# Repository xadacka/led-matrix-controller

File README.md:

Note: This is still beta and will be changing and needs to be tidied up a bit but it all works pretty well, just install it and control it from the web interface. There is a huge update coming soon that redesigns the entire interface and back end, stay tuned for that it'll make the whole thing 10x more usable and stable, along with making it easy too update the animations.

led-matrix-controller
=====================
Web based controller for led panels. This code is designed for Raspberry Pi using HUB75 led panels. You can buy the panels cheap from China, or get them off eBay or adafruit or a multitude of other places.

To use this code, simply run the command below.

```
curl -sSL https://raw.githubusercontent.com/xadacka/led-matrix-controller/master/setup.sh | bash
```

The setup script will install apache2 and move the required files into the web directory and change a few permissions for apache. The only way this can work is by letting www-data (apache, php) access the GPIO pins. By default, they require sudo - the setup script allows www-data to access them. This is a minor security issue but shouldn't be too bad.

Notes on screen size/chain length
----------------------------------
Currently, the code is designed for 4 32x16 panels in series from chain 1 - will soon be adding an option on the web interface for changing how many panels you have and how they're chained. You can manually change this now to add/remove panels by changing the flags in the bash scripts, namely the important ones are as follows.

For text: [piyhon.py](rpi-rgb-led-matrix/examples-api-use/pithon.py)
For clock: [time.sh](rpi-rgb-led-matrix/examples-api-use/time.sh)
For animations: Every script in [scripts](scripts)

Simple change --led-rows=16 to how many pixels high your panels are and --led-chain=4 to the amount of panels you're using.

Automated Setup
---------------
We strongly recommend running raspbian-lite as opposed to the full version, you can download the image [here](https://www.raspberrypi.org/downloads/raspbian/)

You should probably wire the panels before running the scripts as once it's installed, it'll show you the pi's IP on the screen but you can leave that until after if you like. Wiring diagram is [here](./wiring.md)

To use this code, simply run the command below. 

The setup script will clone into /home/pi - as of now it'll only work in this folder.

Of course, piping unknown scripts into bash isn't generally good security policy but if you've any doubts just take a look at the install script yourself and you'll see all is in order.

```
curl -sSL https://raw.githubusercontent.com/xer0design/led-matrix-controller/master/setup.sh | bash
```

This will automate everything and will reboot after, once the reboot is finished you should see your Pi's IP address scrolling across the screen and from there, you can type it into your browser and start using your panel.

The default password for the web interface is "password". Because of course it is. 

Manual Setup
------------
We wouldn't recommend it. But we will add instructions soon. If you want, just open [setup.sh](./setup.sh) to see what's happening, it's all commented out.

Basic configuration
===================

Password Management
-------------------
As default, the password protected access is both not fully enabled, and set to the default password "password". You should fix both of these things in a live environment. If go just type [/sender.php](/www/sender.php) after the pi's ip address, you'll have full control without the need to login. This is useful on closed networks and when testing (so you don't get logged out every few minutes), but to enable password verification for the sender screen, you'll need to edit [sender.php](/www/sender.php) and remove the comments from the first section. This will ensure no one else can access your system. This is especially important considering some scripts can be run with sudo through the web ui - not ideal. 

To change the password, modify [login.php](www/login.php) and edit the third line - obviously, you should also enable password authentication on sender.php as listed above.

Fonts
-----
If you're not too fond of the standard font, American Captain, that's cool, we get it, it's quite easy to change. Edit the file [pithon.py](rpi-rgb-led-matrix/examples-api-use/pithon.py) (yes, we're awful at naming files). You'll see a few examples listed but commented out, just comment out the standard font and uncomment an alternative. If none of them do it for you, you can copy any .ttf font you like into the directory and link to it. In fact, it doesn't even have to be in the same directory. You may have to change the font size when selecting something else. 

Animations
----------
There are many included animations, to use these just select the one you want on the web interface and click submit. I personally use this code myself for work in bars and clubs so the included animations are mostly drinks company logos and the like. I've included a photoshop file animations.psd which should make it easy to drop your own images in and replicate the animations. Or, of course, you can make your own from scratch. To add them to the web interface, edit senders.php to include links to your files, or if you want just point the premade ones to your own files if you don't plan on using mine.

Animations should be made the same size as your display. I.E. if you're using 2 32x16 panels, make sure your animations are 64x16 and so on.) As of 1.5, we cloned the most recent code from [Hzeller](https://github.com/hzeller/rpi-rgb-led-matrix), so we now have video functionality, but we haven't added any standard examples yet. h.264 seems to run very well, so we'd recommend that. 

External Refrences
------------------
You'll see a few refrences to an external folder and also to a few external files, you can ignore these and delete the refrences, or you can make use of them and add in your own external files, or you can just leave them there - it won't effect performance in any meaningful way. I use this code primarily for myself along side another system which the external code controls.

Copyright & Licensing
=====================
We've no doubts you know how GPL 3.0 works, but just to make things extra clear, you're fully allowed to use this code for both personal and commercial use, but you must keep all copyright notices in tact and share your changes under the same conditions. 
You can change the title section of the page if you like, the xer0.design led-matrix-controller vX.X bit with the icon, but the footer must be kept under all circumstances, along with notices inside the code. This code is offered as-is, with no warranty.

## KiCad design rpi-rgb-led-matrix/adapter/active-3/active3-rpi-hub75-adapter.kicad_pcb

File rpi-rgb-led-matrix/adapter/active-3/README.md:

Adapter PCB to support up to 3 panel chains
===========================================

   * Supports up to three panel chains for newer plus models and
     Raspberry Pi 2 that have 40 GPIO pins.
   * Uses HCT245 to level shift signals from 3.3V to 5V and shield
     the Raspberry Pi GPIOs from overloading.
   * Open source KiCAD PCB EDA format.
   * Optional: Pads to power the Pi with 5V, including optional capacitor footprints.
   * Connector for RxD input (literally the only GPIO pin left) in case you want to
     make your panel controlled with a serial interface (3.3V logic level).
   * Provides a way to choose the pinout for different kinds of 64x64 matrixes.
   * (not very pretty layout, was just lazy and let the auto-router generate the first pass)
   * BOM:
     - 4x 74HCT245 or 74AHCT245 in 20-SOIC, 7.5mm package which should make
     it easy to hand-solder. Make sure to get the variant with the **T**: HC**T** or AHC**T**
     (there are also HC or AHC, don't use these).
     - 4x 100nF ceramic capacitor (0805 package)
     - 1x 10kOhm resistor (0805 package). Not critcial, just a pullup (2.2k .. 15k probably ok).
     - 3x 16pin IDC (=2x8) male receptible to connect the panels.
     - 1x 40pin female connector to connect to the RPi.
     - 1x (optional) 22μF .. 100μF capacitor for 5V rail.
   * The Gerber FAB files are provided as [active3-rpi-hub75-adapter-fab.zip](./active3-rpi-hub75-adapter-fab.zip)

The board is also [shared on OSH Park][osh-active3] (not affiliated).

![Preview][rendering]
![Real World][real-world]

Essentially, this is connecting the output pins through level shifting buffers (they
are operated at 5V, but the HCT series chips accept 3.3V input levels from the Pi). The
strobe, OE and clock signals are separately buffered for each connector.

![Schematic][schematic]

## Optional

### Power in

The area on the left has 5V/GND input pads, that allow you to power your Raspberry Pi from
a 5V source ... which you are likely to have as you are powering the LED Matrix. This is often
more convenient than using the USB connector to power the Pi.

If you do that, there are pads to add a capacitor to smooth the supply - two footprints are
provided: C5 and C6 for through-hole or surface mount components. The value is not critical;
I usually use a 22μF/6.3V ceramic capacitor on the C6 pads.

### Choose E-Line for 64x64 panels with 1:32 multiplexing

If you have a 64x64 matrix with 1:32 multiplexing, you need to supply an `E`-address line to it.
While the Address lines `A` to `D` have fixed positions on the Hub75 connector, there
seem to be two different ways to connect the `E` address line: it is either on pin 4 or pin 8
of the connector. So this adapter board provides the flexibility to choose the right pin for
your matrix.

Look at the back of the matrix or the documentation to find out for your specific board where
to connect E.

Once you know that, the jumper area in the bottom left of this adapter board allows to choose
to which pin to connect the E-address line to. The corresponding other pin should be connected
to GND. Simply solder a wire bridge as indicated below (or use a jumper that you can change later).

If you are not using such 64x64 matrix, you can connect both these pins to GND.

Here are the typical configurations:

No 1:32 64x64: to GND    | E-Line on Pin 4   | E-Line on Pin 8|
-------------------------|-------------------|----------------
![][config-default]      |![][config-pin4]   |![][config-pin8]

### Input for serial RxD

If you are not using a 64x64 display that occupies the E-Line, you can use the RxD serial input -
this might come in handy if you are using the display to be controlled by a serial line. Be aware
that the input requires 3.3V level, so if you have a RS232, make sure to first adapt the levels.

[rendering]: ../../img/active3-pcb.png
[config-default]: ../../img/active3-pcb-config-default.png
[config-pin4]: ../../img/active3-pcb-config-pin4.png
[config-pin8]: ../../img/active3-pcb-config-pin8.png
[schematic]: ../../img/active3-schematic.png
[real-world]: ../../img/three-parallel-panels-soic.jpg
[osh-active3]: https://oshpark.com/shared_projects/bFtff2GR

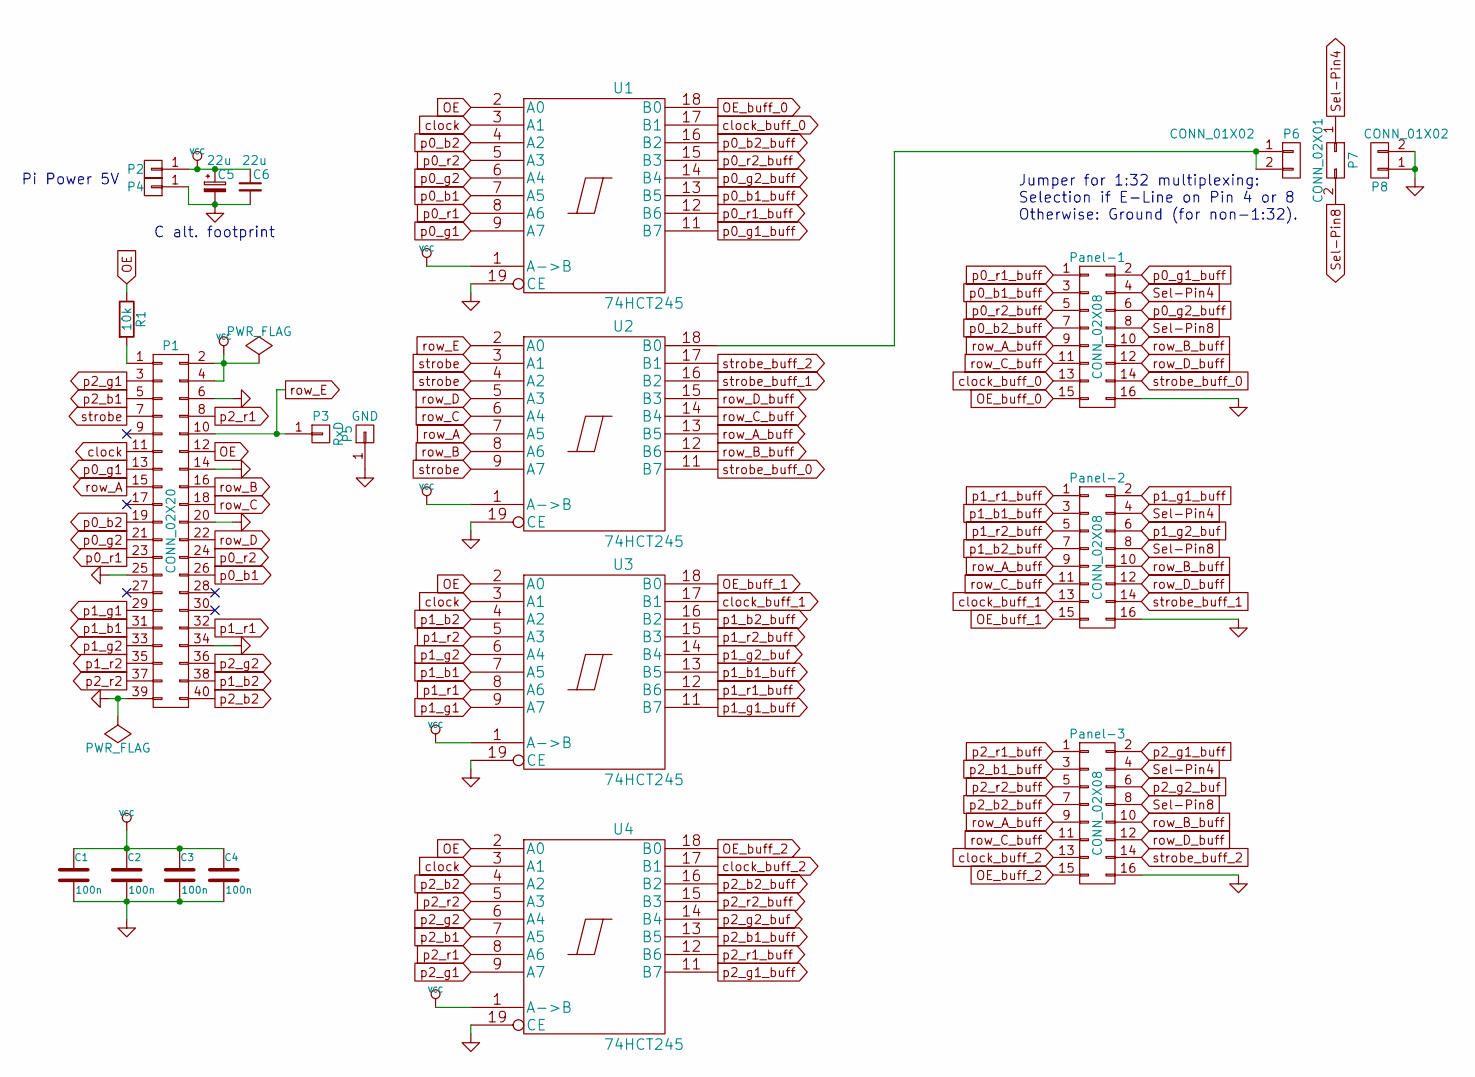
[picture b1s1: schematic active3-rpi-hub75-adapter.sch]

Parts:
C1, C2, C3, C4: 100n; C_0805_HandSoldering
C5: 22u; C_Radial_D6.3_L11.2_P2.5
C6: 22u; C_1206_HandSoldering
P1: CONN_02X20; Pin_Header_Straight_2x20
P2: +5V; Pin_Header_Straight_1x01
P3: RxD; Pin_Header_Straight_1x01
P4, P5: GND; Pin_Header_Straight_1x01
P6, P8: CONN_01X02; Pin_Header_Straight_1x02
P7: CONN_02X01; Pin_Header_Straight_1x02
Panel-1, Panel-2, Panel-3: CONN_02X08; Pin_Header_Straight_2x08
R1: 10k; R_0805_HandSoldering
U1, U2, U3, U4: 74HCT245; SOIC-20_7.5x12.8mm_Pitch1.27mm

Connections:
GND: C1.2, C2.2, C3.2, C4.2, C5.2, C6.2, P1.6, P1.14, P1.20, P1.25, P1.34, P1.39, P4.1, P5.1, P8.1, P8.2, Panel-1.16, Panel-2.16, Panel-3.16, U1.10 (GND), U1.19 (CE), U2.10 (GND), U2.19 (CE), U3.10 (GND), U3.19 (CE), U4.10 (GND), U4.19 (CE)
unnamed: P1.1, R1.2
unnamed: P6.1, P6.2, U2.18 (B0)
OE: P1.12, R1.1, U1.2 (A0), U3.2 (A0), U4.2 (A0)
OE_buff_0: Panel-1.15, U1.18 (B0)
OE_buff_1: Panel-2.15, U3.18 (B0)
OE_buff_2: Panel-3.15, U4.18 (B0)
Sel-Pin4: P7.1, Panel-1.4, Panel-2.4, Panel-3.4
Sel-Pin8: P7.2, Panel-1.8, Panel-2.8, Panel-3.8
VCC: C1.1, C2.1, C3.1, C4.1, C5.1, C6.1, P1.2, P1.4, P2.1, U1.1 (A->B), U1.20 (VCC), U2.1 (A->B), U2.20 (VCC), U3.1 (A->B), U3.20 (VCC), U4.1 (A->B), U4.20 (VCC)
clock: P1.11, U1.3 (A1), U3.3 (A1), U4.3 (A1)
clock_buff_0: Panel-1.13, U1.17 (B1)
clock_buff_1: Panel-2.13, U3.17 (B1)
clock_buff_2: Panel-3.13, U4.17 (B1)
p0_b1: P1.26, U1.7 (A5)
p0_b1_buff: Panel-1.3, U1.13 (B5)
p0_b2: P1.19, U1.4 (A2)
p0_b2_buff: Panel-1.7, U1.16 (B2)
p0_g1: P1.13, U1.9 (A7)
p0_g1_buff: Panel-1.2, U1.11 (B7)
p0_g2: P1.21, U1.6 (A4)
p0_g2_buff: Panel-1.6, U1.14 (B4)
p0_r1: P1.23, U1.8 (A6)
p0_r1_buff: Panel-1.1, U1.12 (B6)
p0_r2: P1.24, U1.5 (A3)
p0_r2_buff: Panel-1.5, U1.15 (B3)
p1_b1: P1.31, U3.7 (A5)
p1_b1_buff: Panel-2.3, U3.13 (B5)
p1_b2: P1.38, U3.4 (A2)
p1_b2_buff: Panel-2.7, U3.16 (B2)
p1_g1: P1.29, U3.9 (A7)
p1_g1_buff: Panel-2.2, U3.11 (B7)
p1_g2: P1.33, U3.6 (A4)
p1_g2_buf: Panel-2.6, U3.14 (B4)
p1_r1: P1.32, U3.8 (A6)
p1_r1_buff: Panel-2.1, U3.12 (B6)
p1_r2: P1.35, U3.5 (A3)
p1_r2_buff: Panel-2.5, U3.15 (B3)
p2_b1: P1.5, U4.7 (A5)
p2_b1_buff: Panel-3.3, U4.13 (B5)
p2_b2: P1.40, U4.4 (A2)
p2_b2_buff: Panel-3.7, U4.16 (B2)
p2_g1: P1.3, U4.9 (A7)
p2_g1_buff: Panel-3.2, U4.11 (B7)
p2_g2: P1.36, U4.6 (A4)
p2_g2_buf: Panel-3.6, U4.14 (B4)
p2_r1: P1.8, U4.8 (A6)
p2_r1_buff: Panel-3.1, U4.12 (B6)
p2_r2: P1.37, U4.5 (A3)
p2_r2_buff: Panel-3.5, U4.15 (B3)
row_A: P1.15, U2.7 (A5)
row_A_buff: Panel-1.9, Panel-2.9, Panel-3.9, U2.13 (B5)
row_B: P1.16, U2.8 (A6)
row_B_buff: Panel-1.10, Panel-2.10, Panel-3.10, U2.12 (B6)
row_C: P1.18, U2.6 (A4)
row_C_buff: Panel-1.11, Panel-2.11, Panel-3.11, U2.14 (B4)
row_D: P1.22, U2.5 (A3)
row_D_buff: Panel-1.12, Panel-2.12, Panel-3.12, U2.15 (B3)
row_E: P1.10, P3.1, U2.2 (A0)
strobe: P1.7, U2.3 (A1), U2.4 (A2), U2.9 (A7)
strobe_buff_0: Panel-1.14, U2.11 (B7)
strobe_buff_1: Panel-2.14, U2.16 (B2)
strobe_buff_2: Panel-3.14, U2.17 (B1)

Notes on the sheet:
Pi Power 5V
C alt. footprint
Jumper for 1:32 multiplexing: Selection if E-Line on Pin 4 or 8 Otherwise: Ground (for non-1:32).

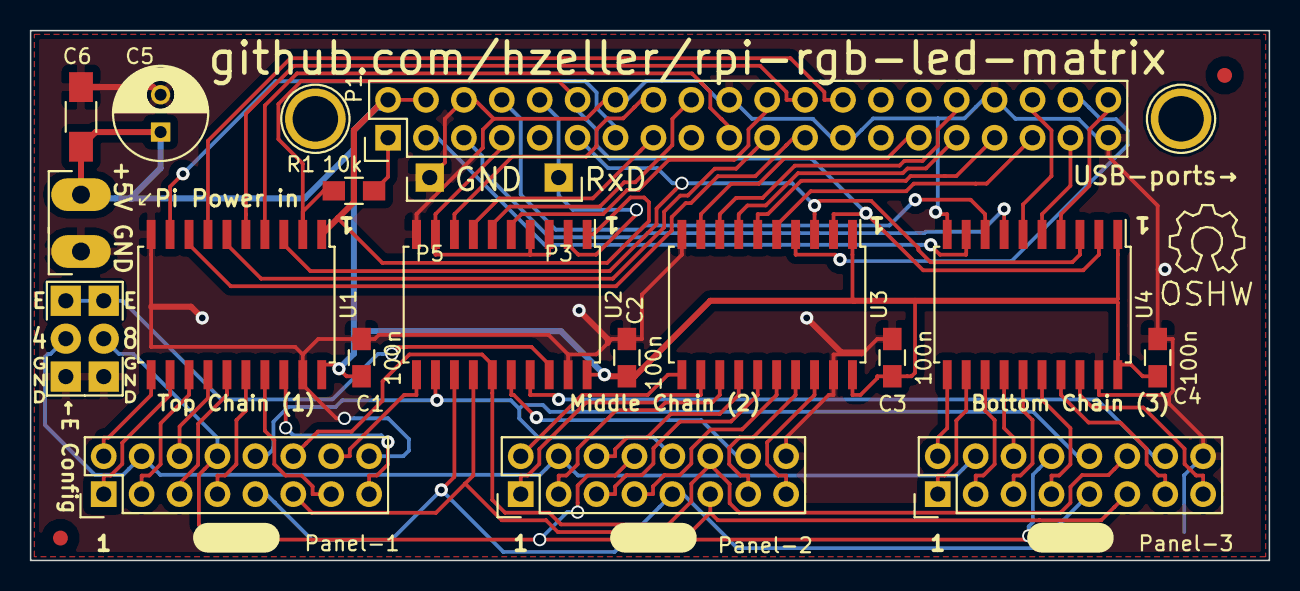
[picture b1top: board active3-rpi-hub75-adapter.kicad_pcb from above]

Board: 2 copper layers, 83.0 x 35.5 mm, 24 parts (0 on the bottom side), 63 nets.

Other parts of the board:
P20, P21: CONN_01X01; 1pin

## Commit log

2017-05-09 Added rpi-rgb-led-matrix codebase.
2017-05-09 Added rpi-rgb-led-matrix
2017-05-09 remove rpi-
2017-05-09 Update README.md
    Added first basic readme info
2017-05-10 Added more info, explained the setup script a bit
2017-05-10 Added functions and comments
2017-05-10 Fixed setup.sh encoding
2017-05-10 Added note on source and last update.
2017-05-11 Update README.md
    Added a warning about it being unfinished code, explained the setup script in a bit more detail.
2017-05-11 Updated setup, added www
2017-05-11 Added c-example
2017-05-11 Added
2017-05-11 Images updated
2017-05-11 Updated to reflect setup script changes
2017-05-11 Removed adapters.
2017-05-11 Modified
2017-05-12 new font
2017-05-12 remove mac .files
2017-05-25 Removed do not use disclaimer
2017-05-25 Added animations explainer
2017-05-25 Removed old code, added comments
2017-05-25 Added comments explaining everything
2017-06-08 fixed boot ip
2017-06-08 new animation added
2017-06-08 added animation
2017-06-11 Moved to scripts folder
2017-06-11 Added video settings
2017-06-11 started adding video
2017-06-11 added video
2017-06-11 added video feature
2017-06-11 Added video exception
2017-06-11 Added video to setup script
2017-06-11 IP address on boot fix.
2017-06-21 updated.
2017-06-21 fixes
2017-06-25 Remove .file
2017-06-25 Added real time clock
2017-06-26 refined
2017-06-28 Changed setup process to ensure correct directory
    No longer clone first then run setup, now curl setup to bash
2017-06-28 Updated install commands to reflect new setup.sh
2017-06-28 Updated to v1.6
2017-06-28 added comments
2017-06-28 Added basic config instructions + GPL warning
2017-06-29 patch
2017-06-30 fixed gpl notice
2017-07-04 Updated to v1.6.2
2017-07-05 Laid out fonts differently for clarity
2017-07-05 Fixed links
2017-07-05 Fixed formatting
2017-07-05 v1.6.2 patches
2017-07-05 added status messages in footer
2017-07-05 Added ui preview
2017-07-26 Updated to 1.6.5
2017-07-26 Added admin
    Started using pihole on the same pi, this will stop the pihole admin from syncing.
2017-09-12 Added internal fs image
2017-09-12 image upgrades
2017-10-02 touchscreen support added
2017-11-07 fixed syntax
2017-11-07 removed update question
2017-11-07 clean up
2017-11-07 fixed symlink not running under root
2017-11-16 fixed missing -y flag
2022-06-17 Update to 22 codebase
2022-06-17 Update README.md
    Updated username.
2022-06-29 Replaced deprecated packages
    Updates to make script work again, haven't tested it in years and half the packages failed and needed to be replaced.
